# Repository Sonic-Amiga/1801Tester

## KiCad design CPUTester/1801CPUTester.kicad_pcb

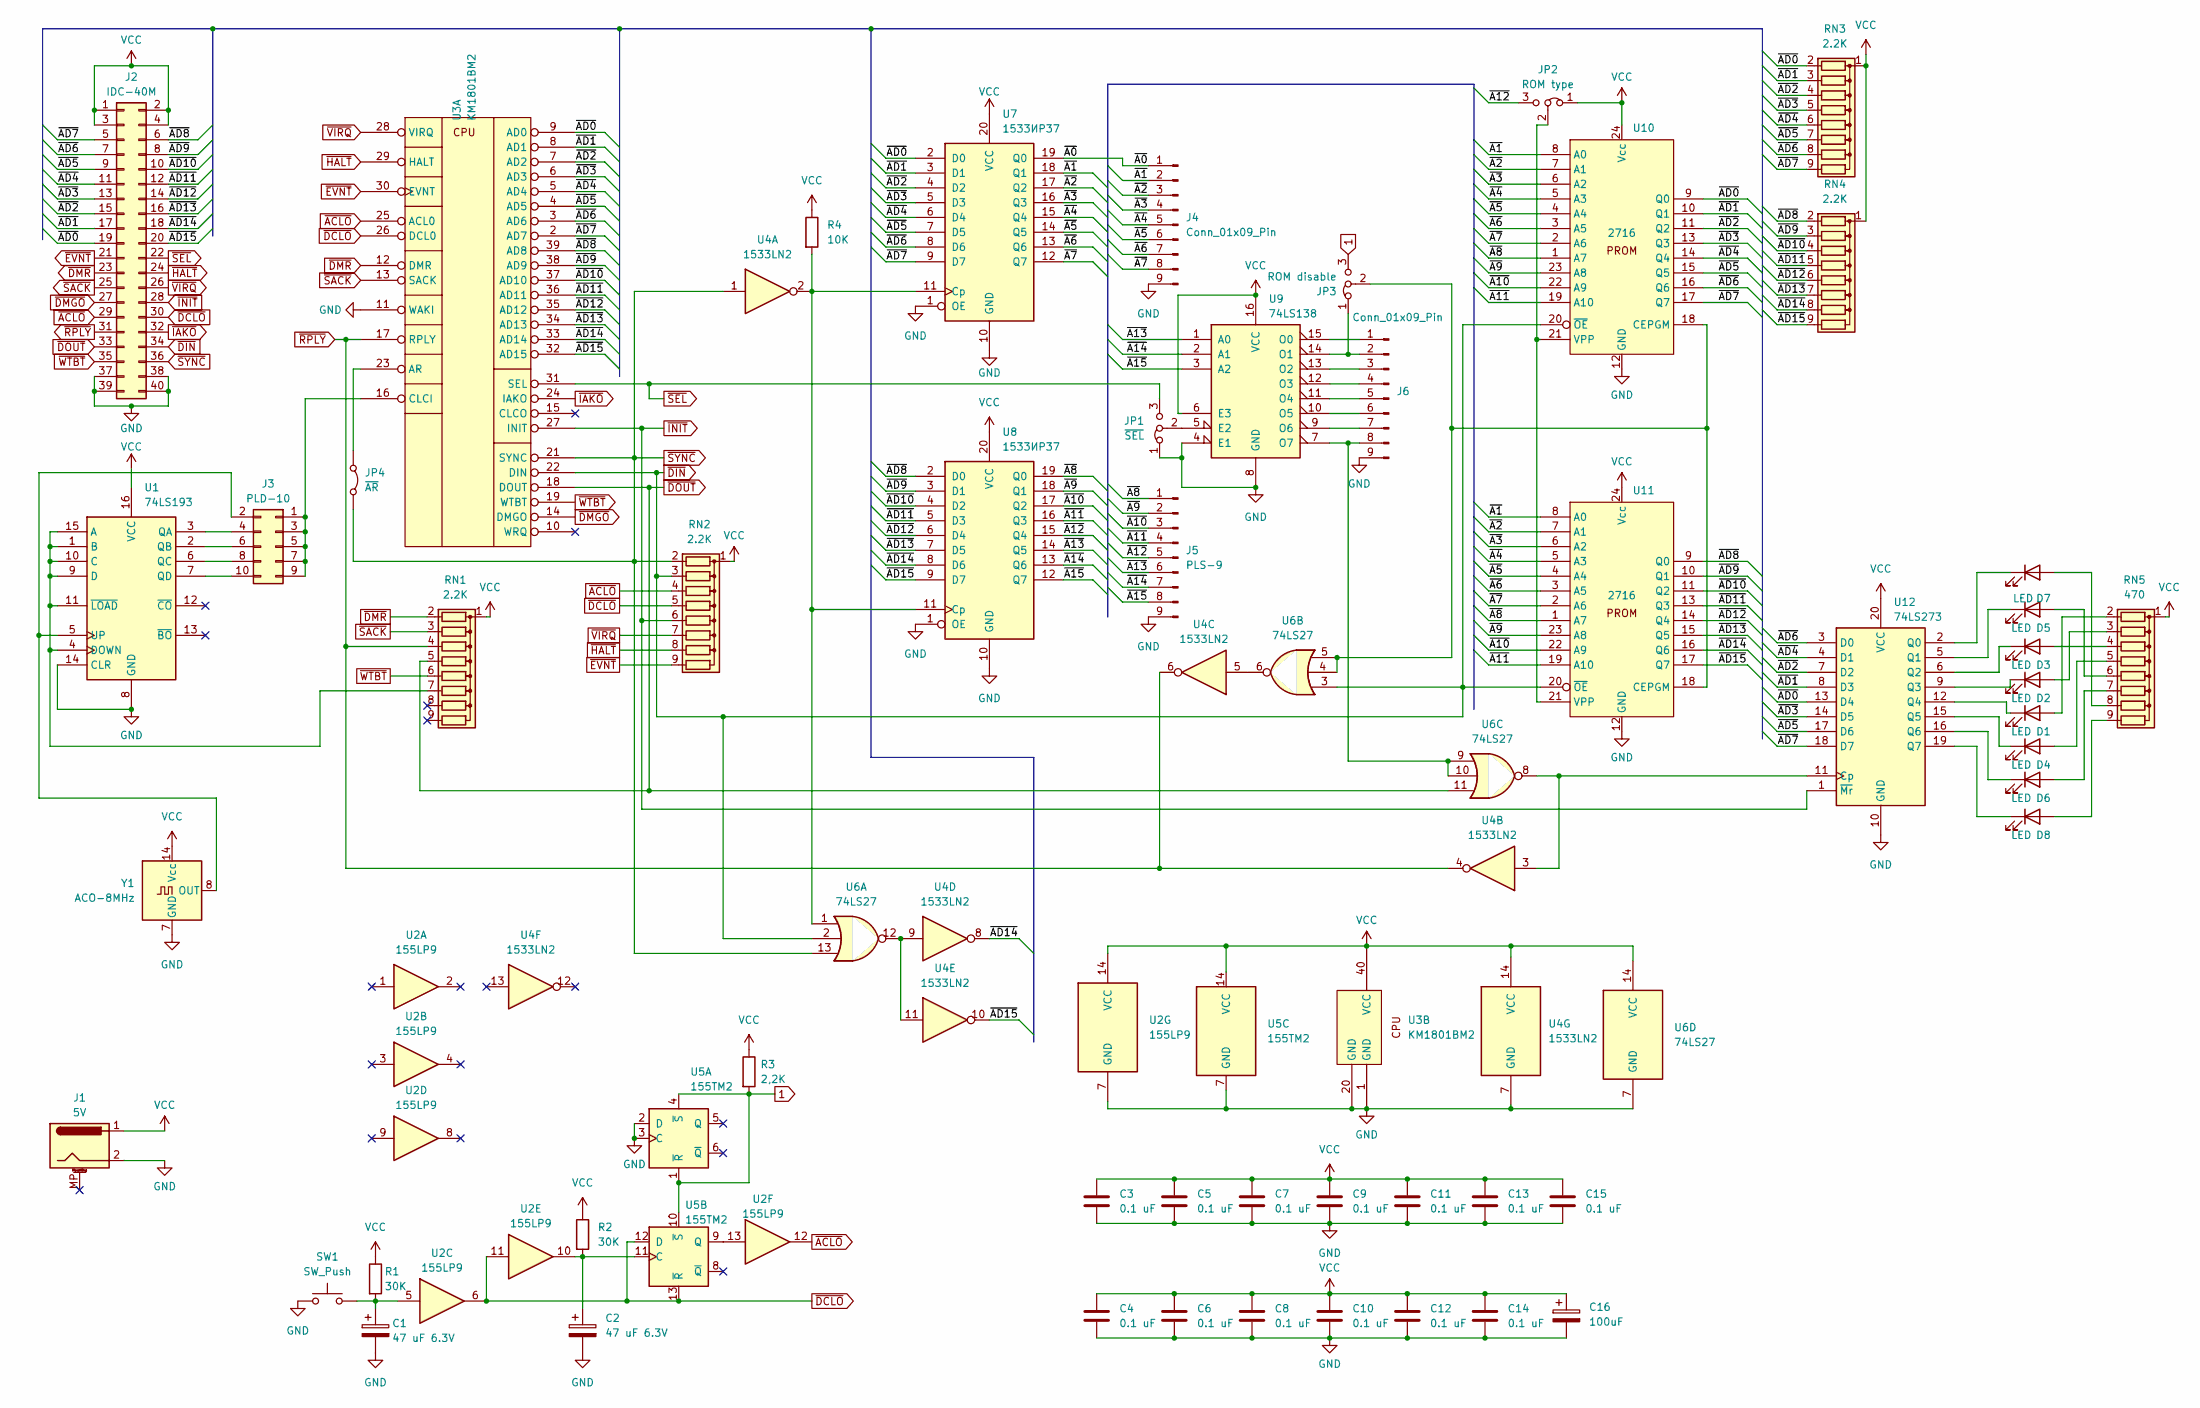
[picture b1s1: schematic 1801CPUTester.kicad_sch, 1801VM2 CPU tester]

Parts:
C1, C2: 47 uF 6.3V; CP_Radial_D6.3mm_P2.50mm
C3, C4, C5, C6, C7, C8, C9, C10, C11, C12, C13, C14, C15: 0.1 uF; C_Disc_D6.0mm_W2.5mm_P5.00mm
C16: 100uF; CP_Radial_D8.0mm_P3.80mm
D1, D2, D3, D4, D5, D6, D7, D8: LED; LED_D5.0mm
J1: 5V; BarrelJack_Horizontal
J2: IDC-40M; IDC-Header_2x20_P2.54mm_Vertical
J3: PLD-10; PinHeader_2x05_P2.54mm_Vertical
J4, J6: Conn_01x09_Pin; PinHeader_1x09_P2.54mm_Vertical
J5: PLS-9; PinHeader_1x09_P2.54mm_Vertical
JP1: ~{SEL}; PinHeader_1x03_P2.54mm_Vertical
JP2: ROM type; PinHeader_1x03_P2.54mm_Vertical
JP3: ROM disable; PinHeader_1x03_P2.54mm_Vertical
JP4: ~{AR}; PinHeader_1x02_P2.54mm_Vertical
R1, R2: 30K; R_Axial_DIN0204_L3.6mm_D1.6mm_P7.62mm_Horizontal
R3: 2,2K; R_Axial_DIN0204_L3.6mm_D1.6mm_P7.62mm_Horizontal
R4: 10K; R_Axial_DIN0204_L3.6mm_D1.6mm_P7.62mm_Horizontal
RN1, RN2, RN3, RN4: 2.2K; R_Array_SIP9
RN5: 470; R_Array_SIP9
SW1: SW_Push; SW_PUSH_6mm
U1: 74LS193; DIP-16_W7.62mm
U2: 155LP9; DIP-14_W7.62mm
U3: КМ1801ВМ2; DIP_Socket-40_W11.9mm_W12.7mm_W15.24mm_W17.78mm_W18.5mm_3M_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
U4: 1533LN2; DIP-14_W7.62mm
U5: 155TM2; DIP-14_W7.62mm
U6: 74LS27; DIP-14_W7.62mm
U7, U8: 1533ИР37; DIP-20_W7.62mm
U9: 74LS138; DIP-16_W7.62mm
U10, U11: 2716; DIP-24_W15.24mm_Socket
U12: 74LS273; DIP-20_W7.62mm
Y1: ACO-8MHz; Oscillator_DIP-14

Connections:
1: JP3.3 (B), R3.2, U5.1 (~R), U5.4 (~S), U5.10 (~S)
/~A0: J4.1, U7.19 (Q0)
/~A1: J4.2, U7.18 (Q1), U10.8 (A0), U11.8 (A0)
/~A2: J4.3, U7.17 (Q2), U10.7 (A1), U11.7 (A1)
/~A3: J4.4, U7.16 (Q3), U10.6 (A2), U11.6 (A2)
/~A4: J4.5, U7.15 (Q4), U10.5 (A3), U11.5 (A3)
/~A5: J4.6, U7.14 (Q5), U10.4 (A4), U11.4 (A4)
/~A6: J4.7, U7.13 (Q6), U10.3 (A5), U11.3 (A5)
/~A7: J4.8, U7.12 (Q7), U10.2 (A6), U11.2 (A6)
/~A8: J5.1, U8.19 (Q0), U10.1 (A7), U11.1 (A7)
/~A9: J5.2, U8.18 (Q1), U10.23 (A8), U11.23 (A8)
/~A10: J5.3, U8.17 (Q2), U10.22 (A9), U11.22 (A9)
/~A11: J5.4, U8.16 (Q3), U10.19 (A10), U11.19 (A10)
/~A12: J5.5, JP2.3 (B), U8.15 (Q4)
/~A13: J5.6, U8.14 (Q5), U9.1 (A0)
/~A14: J5.7, U8.13 (Q6), U9.2 (A1)
/~A15: J5.8, U8.12 (Q7), U9.3 (A2)
/~AD0: J2.19, RN3.2 (R1), U3.9 (AD0), U7.2 (D0), U10.9 (Q0), U12.13 (D4)
/~AD1: J2.17, RN3.3 (R2), U3.8 (AD1), U7.3 (D1), U10.10 (Q1), U12.8 (D3)
/~AD2: J2.15, RN3.4 (R3), U3.7 (AD2), U7.4 (D2), U10.11 (Q2), U12.7 (D2)
/~AD3: J2.13, RN3.5 (R4), U3.6 (AD3), U7.5 (D3), U10.13 (Q3), U12.14 (D5)
/~AD4: J2.11, RN3.6 (R5), U3.5 (AD4), U7.6 (D4), U10.14 (Q4), U12.4 (D1)
/~AD5: J2.9, RN3.7 (R6), U3.4 (AD5), U7.7 (D5), U10.15 (Q5), U12.17 (D6)
/~AD6: J2.7, RN3.8 (R7), U3.3 (AD6), U7.8 (D6), U10.16 (Q6), U12.3 (D0)
/~AD7: J2.5, RN3.9 (R8), U3.2 (AD7), U7.9 (D7), U10.17 (Q7), U12.18 (D7)
/~AD8: J2.6, RN4.2 (R1), U3.39 (AD8), U8.2 (D0), U11.9 (Q0)
/~AD9: J2.8, RN4.3 (R2), U3.38 (AD9), U8.3 (D1), U11.10 (Q1)
/~AD10: J2.10, RN4.4 (R3), U3.37 (AD10), U8.4 (D2), U11.11 (Q2)
/~AD11: J2.12, RN4.5 (R4), U3.36 (AD11), U8.5 (D3), U11.13 (Q3)
/~AD12: J2.14, RN4.6 (R5), U3.35 (AD12), U8.6 (D4), U11.14 (Q4)
/~AD13: J2.16, RN4.7 (R6), U3.34 (AD13), U8.7 (D5), U11.15 (Q5)
/~AD14: J2.18, RN4.8 (R7), U3.33 (AD14), U4.8, U8.8 (D6), U11.16 (Q6)
/~AD15: J2.20, RN4.9 (R8), U3.32 (AD15), U4.10, U8.9 (D7), U11.17 (Q7)
GND: C1.2, C2.2, C3.2, C4.2, C5.2, C6.2, C7.2, C8.2, C9.2, C10.2, C11.2, C12.2, C13.2, C14.2, C15.2, C16.2, J1.2, J2.37, J2.38, J2.39, J2.40, J4.9, J5.9, J6.9, JP1.1 (A), SW1.1, U1.8 (GND), U1.14 (CLR), U2.7 (GND), U3.1 (GND), U3.11 (WAKI), U3.20 (GND), U4.7 (GND), U5.2 (D), U5.3 (C), U5.7 (GND), U6.7 (GND), U7.1 (OE), U7.10 (GND), U8.1 (OE), U8.10 (GND), U9.4 (E1), U9.8 (GND), U10.12 (GND), U11.12 (GND), U12.10 (GND), Y1.7 (GND)
unnamed: C1.1, R1.2, SW1.2, U2.5
unnamed: D1.2 (A), RN5.2 (R1)
unnamed: D1.1 (K), U12.12 (Q4)
unnamed: D2.2 (A), RN5.3 (R2)
unnamed: D2.1 (K), U12.9 (Q3)
unnamed: D3.2 (A), RN5.4 (R3)
unnamed: D3.1 (K), U12.6 (Q2)
unnamed: D4.2 (A), RN5.5 (R4)
unnamed: D4.1 (K), U12.15 (Q5)
unnamed: D5.2 (A), RN5.6 (R5)
unnamed: D5.1 (K), U12.5 (Q1)
unnamed: D6.2 (A), RN5.7 (R6)
unnamed: D6.1 (K), U12.16 (Q6)
unnamed: D7.2 (A), RN5.8 (R7)
unnamed: D7.1 (K), U12.2 (Q0)
unnamed: D8.2 (A), RN5.9 (R8)
unnamed: D8.1 (K), U12.19 (Q7)
unnamed: J3.1, J3.3, J3.5, J3.7, J3.9, U3.16 (CLCI)
unnamed: J3.2, U1.5 (UP), Y1.8 (OUT)
unnamed: J3.4, U1.3 (QA)
unnamed: J3.6, U1.2 (QB)
unnamed: J3.8, U1.6 (QC)
unnamed: J3.10, U1.7 (QD)
unnamed: J6.1, U9.15 (O0)
unnamed: J6.2, JP3.1 (A), U9.14 (O1)
unnamed: J6.3, U9.13 (O2)
unnamed: J6.4, U9.12 (O3)
unnamed: J6.5, U9.11 (O4)
unnamed: J6.6, U9.10 (O5)
unnamed: J6.7, U9.9 (O6)
unnamed: J6.8, U6.9, U6.10, U9.7 (O7)
unnamed: JP1.2 (C), U9.5 (E2)
unnamed: JP2.2 (C), U10.21 (VPP), U11.21 (VPP)
unnamed: JP3.2 (C), U6.4, U6.5, U10.18 (CEPGM), U11.18 (CEPGM)
unnamed: JP4.1 (A), U3.23 (AR)
unnamed: RN1.7 (R6), U1.1 (B), U1.4 (DOWN), U1.9 (D), U1.10 (C), U1.11 (~LOAD), U1.15 (A)
unnamed: U4.5, U6.6
unnamed: U4.9, U4.11, U6.12
unnamed: C2.1, R2.2, U2.10, U5.11 (C)
unnamed: U2.13, U5.9 (Q)
unnamed: R4.2, U4.2, U6.1, U7.11 (Cp), U8.11 (Cp)
unnamed: U4.3, U6.8, U12.11 (Cp)
VCC: C3.1, C4.1, C5.1, C6.1, C7.1, C8.1, C9.1, C10.1, C11.1, C12.1, C13.1, C14.1, C15.1, C16.1, J1.1, J2.1, J2.2, J2.3, J2.4, JP2.1 (A), R1.1, R2.1, R3.1, R4.1, RN1.1 (common), RN2.1 (common), RN3.1 (common), RN4.1 (common), RN5.1 (common), U1.16 (VCC), U2.14 (VCC), U3.40 (VCC), U4.14 (VCC), U5.14 (VCC), U6.14 (VCC), U7.20 (VCC), U8.20 (VCC), U9.6 (E3), U9.16 (VCC), U10.24 (Vcc), U11.24 (Vcc), U12.20 (VCC), Y1.14 (Vcc)
~ACLO: J2.29, RN2.4 (R3), U2.12, U3.25 (ACL0)
~DCLO: J2.30, RN2.5 (R4), U2.6, U2.11, U3.26 (DCL0), U5.12 (D), U5.13 (~R)
~DIN: J2.34, RN2.3 (R2), U3.22 (DIN), U6.2, U6.3, U10.20 (~OE), U11.20 (~OE)
~DMGO: J2.27, U3.14 (DMGO)
~DMR: J2.23, RN1.2 (R1), U3.12 (DMR)
~DOUT: J2.33, RN1.5 (R4), U3.18 (DOUT), U6.11
~EVNT: J2.21, RN2.9 (R8), U3.30 (EVNT)
~HALT: J2.24, RN2.8 (R7), U3.29 (HALT)
~IAKO: J2.32, U3.24 (IAKO)
~INIT: J2.28, RN2.6 (R5), U3.27 (INIT), U12.1 (~Mr)
~RPLY: J2.31, RN1.4 (R3), U3.17 (RPLY), U4.4, U4.6
~SACK: J2.25, RN1.3 (R2), U3.13 (SACK)
~SEL: J2.22, JP1.3 (B), U3.31 (SEL)
~SYNC: J2.36, JP4.2 (B), RN2.2 (R1), U3.21 (SYNC), U4.1, U6.13
~VIRQ: J2.26, RN2.7 (R6), U3.28 (VIRQ)
~WTBT: J2.35, RN1.6 (R5), U3.19 (WTBT)

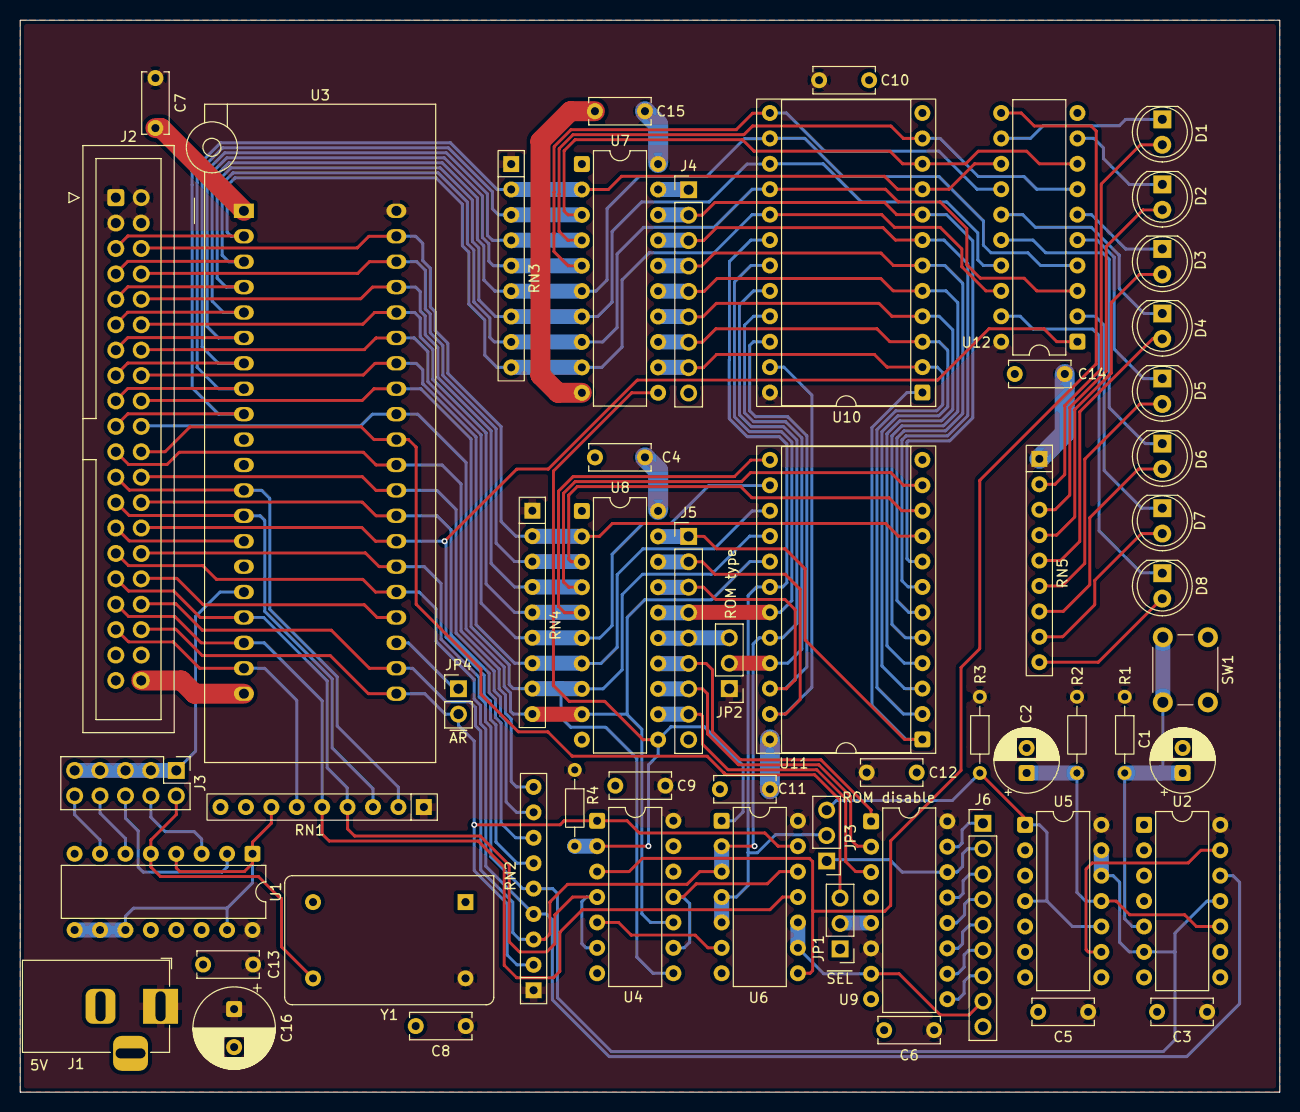
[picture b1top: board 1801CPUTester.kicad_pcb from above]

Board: 2 copper layers, 125.9 x 107.1 mm, 57 parts (0 on the bottom side), 93 nets.

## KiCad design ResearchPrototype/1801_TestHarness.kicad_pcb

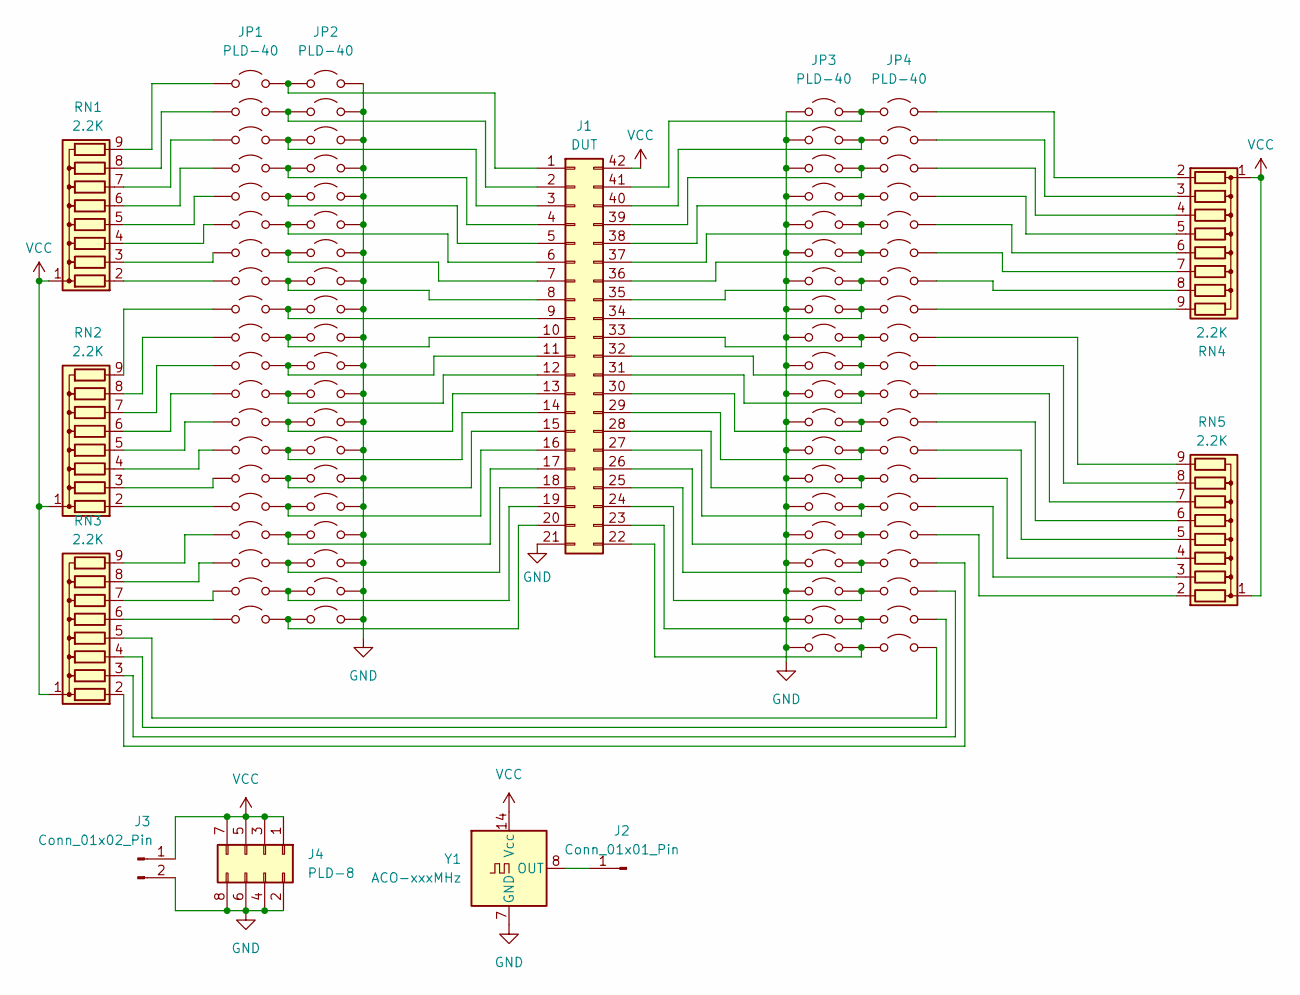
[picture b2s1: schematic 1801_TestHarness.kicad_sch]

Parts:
J1: DUT; 1801_DUT
J2: Conn_01x01_Pin; PinHeader_1x01_P2.54mm_Vertical
J3: Conn_01x02_Pin; JST_NV_B02P-NV_1x02_P5.00mm_Vertical
J4: PLD-8; PinHeader_2x04_P2.54mm_Vertical
JP1, JP2, JP3, JP4: PLD-40; PinHeader_2x20_P2.54mm_Vertical
RN1, RN2, RN3, RN4, RN5: 2.2K; R_Array_SIP9
Y1: ACO-xxxMHz; Oscillator_DIP-14

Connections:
GND: J1.21, J3.2, J4.2, J4.4, J4.6, J4.8, JP2.2 (B), JP2.4 (B), JP2.6 (B), JP2.8 (B), JP2.10 (B), JP2.12 (B), JP2.14 (B), JP2.16 (B), JP2.18 (B), JP2.20 (B), JP2.22 (B), JP2.24 (B), JP2.26 (B), JP2.28 (B), JP2.30 (B), JP2.32 (B), JP2.34 (B), JP2.36 (B), JP2.38 (B), JP2.40 (B), JP3.1 (A), JP3.3 (A), JP3.5 (A), JP3.7 (A), JP3.9 (A), JP3.11 (A), JP3.13 (A), JP3.15 (A), JP3.17 (A), JP3.19 (A), JP3.21 (A), JP3.23 (A), JP3.25 (A), JP3.27 (A), JP3.29 (A), JP3.31 (A), JP3.33 (A), JP3.35 (A), JP3.37 (A), JP3.39 (A), Y1.7 (GND)
unnamed: J1.1, JP1.2 (B), JP2.1 (A)
unnamed: J1.2, JP1.4 (B), JP2.3 (A)
unnamed: J1.3, JP1.6 (B), JP2.5 (A)
unnamed: J1.4, JP1.8 (B), JP2.7 (A)
unnamed: J1.5, JP1.10 (B), JP2.9 (A)
unnamed: J1.6, JP1.12 (B), JP2.11 (A)
unnamed: J1.7, JP1.14 (B), JP2.13 (A)
unnamed: J1.8, JP1.16 (B), JP2.15 (A)
unnamed: J1.9, JP1.18 (B), JP2.17 (A)
unnamed: J1.10, JP1.20 (B), JP2.19 (A)
unnamed: J1.11, JP1.22 (B), JP2.21 (A)
unnamed: J1.12, JP1.24 (B), JP2.23 (A)
unnamed: J1.13, JP1.26 (B), JP2.25 (A)
unnamed: J1.14, JP1.28 (B), JP2.27 (A)
unnamed: J1.15, JP1.30 (B), JP2.29 (A)
unnamed: J1.16, JP1.32 (B), JP2.31 (A)
unnamed: J1.17, JP1.34 (B), JP2.33 (A)
unnamed: J1.18, JP1.36 (B), JP2.35 (A)
unnamed: J1.19, JP1.38 (B), JP2.37 (A)
unnamed: J1.20, JP1.40 (B), JP2.39 (A)
unnamed: J1.22, JP3.40 (B), JP4.39 (A)
unnamed: J1.23, JP3.38 (B), JP4.37 (A)
unnamed: J1.24, JP3.36 (B), JP4.35 (A)
unnamed: J1.25, JP3.34 (B), JP4.33 (A)
unnamed: J1.26, JP3.32 (B), JP4.31 (A)
unnamed: J1.27, JP3.30 (B), JP4.29 (A)
unnamed: J1.28, JP3.28 (B), JP4.27 (A)
unnamed: J1.29, JP3.26 (B), JP4.25 (A)
unnamed: J1.30, JP3.24 (B), JP4.23 (A)
unnamed: J1.31, JP3.22 (B), JP4.21 (A)
unnamed: J1.32, JP3.20 (B), JP4.19 (A)
unnamed: J1.33, JP3.18 (B), JP4.17 (A)
unnamed: J1.34, JP3.16 (B), JP4.15 (A)
unnamed: J1.35, JP3.14 (B), JP4.13 (A)
unnamed: J1.36, JP3.12 (B), JP4.11 (A)
unnamed: J1.37, JP3.10 (B), JP4.9 (A)
unnamed: J1.38, JP3.8 (B), JP4.7 (A)
unnamed: J1.39, JP3.6 (B), JP4.5 (A)
unnamed: J1.40, JP3.4 (B), JP4.3 (A)
unnamed: J1.41, JP3.2 (B), JP4.1 (A)
unnamed: J2.1 (Pin_1_1), Y1.8 (OUT)
unnamed: JP1.15 (A), RN1.2 (R1)
unnamed: JP1.13 (A), RN1.3 (R2)
unnamed: JP1.11 (A), RN1.4 (R3)
unnamed: JP1.9 (A), RN1.5 (R4)
unnamed: JP1.7 (A), RN1.6 (R5)
unnamed: JP1.5 (A), RN1.7 (R6)
unnamed: JP1.3 (A), RN1.8 (R7)
unnamed: JP1.1 (A), RN1.9 (R8)
unnamed: JP1.31 (A), RN2.2 (R1)
unnamed: JP1.29 (A), RN2.3 (R2)
unnamed: JP1.27 (A), RN2.4 (R3)
unnamed: JP1.25 (A), RN2.5 (R4)
unnamed: JP1.23 (A), RN2.6 (R5)
unnamed: JP1.21 (A), RN2.7 (R6)
unnamed: JP1.19 (A), RN2.8 (R7)
unnamed: JP1.17 (A), RN2.9 (R8)
unnamed: JP4.34 (B), RN3.2 (R1)
unnamed: JP4.36 (B), RN3.3 (R2)
unnamed: JP4.38 (B), RN3.4 (R3)
unnamed: JP4.40 (B), RN3.5 (R4)
unnamed: JP1.39 (A), RN3.6 (R5)
unnamed: JP1.37 (A), RN3.7 (R6)
unnamed: JP1.35 (A), RN3.8 (R7)
unnamed: JP1.33 (A), RN3.9 (R8)
unnamed: JP4.2 (B), RN4.2 (R1)
unnamed: JP4.4 (B), RN4.3 (R2)
unnamed: JP4.6 (B), RN4.4 (R3)
unnamed: JP4.8 (B), RN4.5 (R4)
unnamed: JP4.10 (B), RN4.6 (R5)
unnamed: JP4.12 (B), RN4.7 (R6)
unnamed: JP4.14 (B), RN4.8 (R7)
unnamed: JP4.16 (B), RN4.9 (R8)
unnamed: JP4.32 (B), RN5.2 (R1)
unnamed: JP4.30 (B), RN5.3 (R2)
unnamed: JP4.28 (B), RN5.4 (R3)
unnamed: JP4.26 (B), RN5.5 (R4)
unnamed: JP4.24 (B), RN5.6 (R5)
unnamed: JP4.22 (B), RN5.7 (R6)
unnamed: JP4.20 (B), RN5.8 (R7)
unnamed: JP4.18 (B), RN5.9 (R8)
VCC: J1.42, J3.1, J4.1, J4.3, J4.5, J4.7, RN1.1 (common), RN2.1 (common), RN3.1 (common), RN4.1 (common), RN5.1 (common), Y1.14 (Vcc)

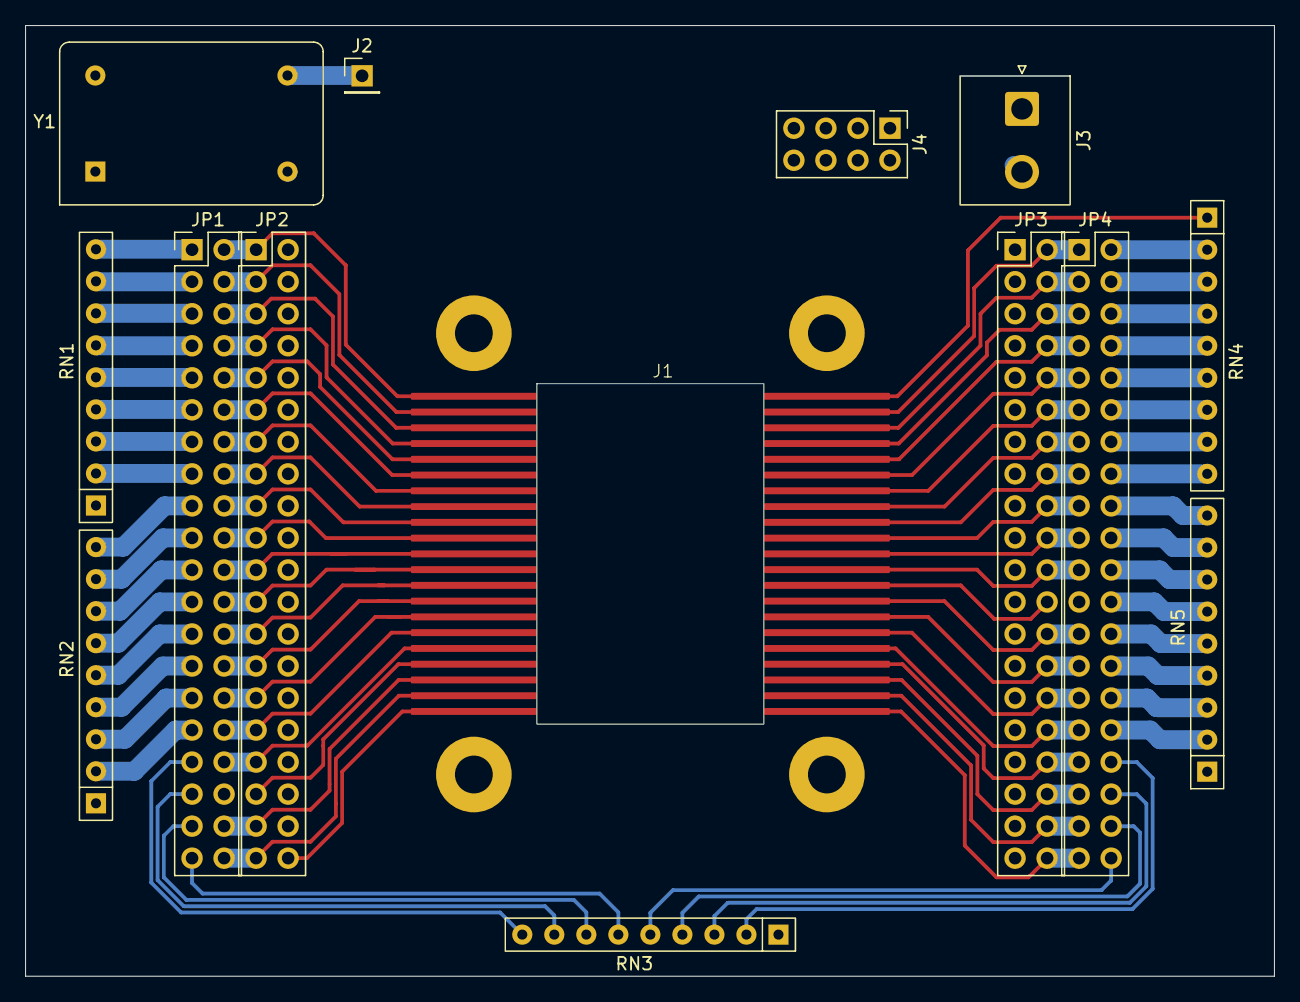
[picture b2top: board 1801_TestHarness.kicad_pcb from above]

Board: 2 copper layers, 99.1 x 75.4 mm, 14 parts (0 on the bottom side), 83 nets.
